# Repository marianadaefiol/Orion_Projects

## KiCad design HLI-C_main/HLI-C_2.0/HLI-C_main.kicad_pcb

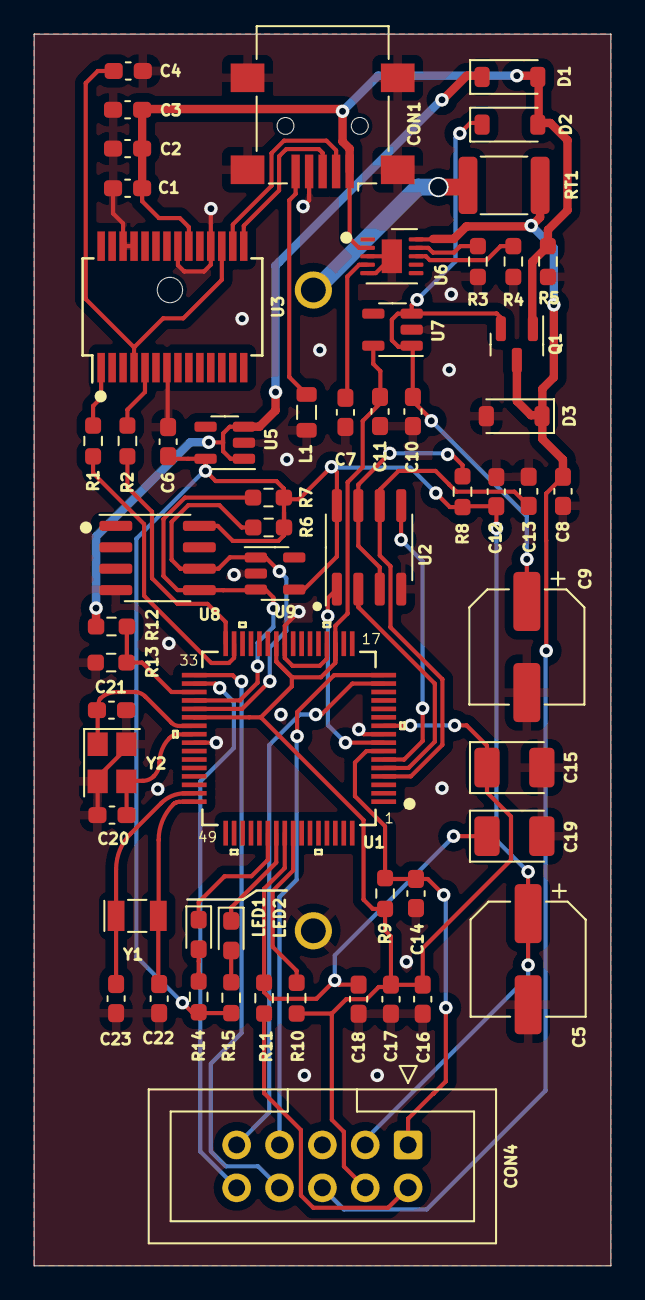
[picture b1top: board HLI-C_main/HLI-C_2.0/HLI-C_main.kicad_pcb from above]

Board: 2 copper layers, 34.2 x 73.0 mm, 59 parts (0 on the bottom side), 42 nets.

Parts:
C1, C6, C8, C10, C12, C16, C17, C18: 100nF; C_0603_1608Metric_Pad1.08x0.95mm_HandSolder
C2: 10nF; C_0603_1608Metric_Pad1.08x0.95mm_HandSolder
C3: 4,7uF; C_0603_1608Metric_Pad1.08x0.95mm_HandSolder
C4, C7, C11: 1uF; C_0603_1608Metric_Pad1.08x0.95mm_HandSolder
C5, C9: 220uFx16V; CP_Elec_6.3x7.7
C13: 47pF; C_0603_1608Metric_Pad1.08x0.95mm_HandSolder
C14: 1nF; C_0603_1608Metric_Pad1.08x0.95mm_HandSolder
C15: 10UfX6V-Tan; CP_EIA-3528-12_Kemet-T_Pad1.50x2.35mm_HandSolder
C19: 10uFx6V-Tan; CP_EIA-3528-12_Kemet-T_Pad1.50x2.35mm_HandSolder
C20, C21: 20pF; C_0603_1608Metric_Pad1.08x0.95mm_HandSolder
C22, C23: 12pF; C_0603_1608Metric_Pad1.08x0.95mm_HandSolder
CON1: USB_B; USB_Mini-B_Lumberg_2486_01_Horizontal
CON3: CR123A; BAT_BH123A
CON4: Conector_gravação; IDC-Header_2x05_P2.54mm_Vertical
D1, D2, D3: DSS14U; D_SOD-123
L1: BLM21PG221SN1D; L_0805_2012Metric
LED1: RED; LED_0603_1608Metric_Pad1.05x0.95mm_HandSolder
LED2: GREEN; LED_0603_1608Metric_Pad1.05x0.95mm_HandSolder
Q1: DMP3068L-7; SOT-23
R1, R2, R14, R15: 470R; R_0603_1608Metric_Pad0.98x0.95mm_HandSolder
R3: 10k; R_0603_1608Metric_Pad0.98x0.95mm_HandSolder
R4: 3.3k; R_0603_1608Metric_Pad0.98x0.95mm_HandSolder
R5, R8, R9: 22k; R_0603_1608Metric_Pad0.98x0.95mm_HandSolder
R6, R7, R11: 1K; R_0603_1608Metric_Pad0.98x0.95mm_HandSolder
R10: 22K; R_0603_1608Metric_Pad0.98x0.95mm_HandSolder
R12: 1K8; R_0603_1608Metric_Pad0.98x0.95mm_HandSolder
R13: 3K3; R_0603_1608Metric_Pad0.98x0.95mm_HandSolder
RT1: 300mA - 304N; R_1812_4532Metric
U1: PIC24HJ64GP206-I_PT; PIC24HJ64GP206-I_slash_PT
U2: FM25V10-GTR; SOIC-8_3.9x4.9mm_P1.27mm
U3: FT232RL; SSOP-28_5.3x10.2mm_P0.65mm
U5, U7: TPS7A0533PDBV; SOT-23-5
U6: LM3658SD; VSON-10-1EP_3x3mm_P0.5mm_EP1.2x2mm
U8: ATSHA204A-SSHDA-B; SOIC-8_3.9x4.9mm_P1.27mm
U9: 24AA02-OT; SOT-23-5
Y1: Crystal_32KHz; Crystal_SMD_MicroCrystal_CC7V-T1A-2Pin_3.2x1.5mm
Y2: Crystal_20MHz; Crystal_SMD_TXC_7M-4Pin_3.2x2.5mm

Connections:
0: C1.2, C2.2, C3.2, C4.2, C5.2, C6.2, C7.2, C8.2, C9.2, C10.2, C11.2, C12.2, C13.2, C14.2, C15.2, C16.2, C17.2, C18.2, C19.2, C20.2, C21.2, C22.2, C23.2, CON1.4 (GND), CON1.6, CON3.N, CON4.5, D3.2 (A), L1.1, R3.2, R4.1, R5.2, R13.1, U1.9 (VSS), U1.20 (AVSS), U1.25 (VSS), U1.41 (VSS), U2.4 (VSS), U3.7 (GND), U3.18 (GND), U3.21 (GND), U3.25 (AGND), U3.26 (TEST), U5.2 (GND), U6.3 (GND), U6.5 (EN_B), U6.11 (DAP), U7.2 (GND), U8.4 (GND), U9.2 (GND), Y2.2, Y2.4
+2V5: CON4.2, R11.1
+3.3VP: C11.1, C15.1, C16.1, C17.1, CON4.4, R9.1, R10.1, U1.10 (VDD), U1.19 (AVDD), U1.26 (VDD), U1.38 (VDD), U7.5 (OUT)
+3V3: C5.1, C6.1, C12.1, CON4.3, R6.1, R7.1, R8.1, R14.1, R15.1, U2.8 (VDD), U5.5 (OUT), U8.8 (VCC), U9.4 (VCC)
+5V: C1.1, C2.1, C3.1, CON1.1 (VBUS), D1.2 (A), D2.2 (A), Q1.1 (G), R5.1, U3.20 (VCC), U6.2 (USBPWR)
+5VD: D1.1 (K), R12.2, U5.1 (IN), U5.3 (EN)
LED2: LED1.1 (K), U1.54 (RD6)
LED3: LED2.1 (K), U1.55 (RD7)
unnamed: CON1.3 (D+), U3.15 (USBD+)
unnamed: CON1.2 (D-), U3.16 (USBD-)
unnamed: CON1.5 (Shield), L1.2
unnamed: C9.1, C10.1, D2.1 (K), Q1.2 (S), U7.1 (IN), U7.3 (EN)
unnamed: LED1.2 (A), R14.2
unnamed: LED2.2 (A), R15.2
unnamed: R10.2, U1.57 (VDD)
unnamed: U1.8 (*SS2/RG9), U2.1 (*S)
unnamed: C21.1, U1.39 (OSC1/CLKIN), Y2.1
unnamed: C20.1, U1.40 (OSC2/CLKO), Y2.3
unnamed: C23.1, U1.47 (RC13), Y1.1
unnamed: C22.1, U1.48 (RC14), Y1.2
unnamed: C13.1, U1.4 (SCK2/RG6), U2.6 (C)
unnamed: U1.5 (SDI2/RG7), U2.2 (Q)
unnamed: U1.6 (SDO2/RG8), U2.5 (D)
unnamed: C18.1, C19.1, R11.2, U1.56 (VDDCORE)
unnamed: R8.2, U2.3 (*W), U2.7 (*HOLD)
unnamed: C4.1, U3.4 (VCCIO), U3.17 (3V3OUT)
unnamed: R2.1, U3.5 (RXD)
unnamed: R1.1, U3.1 (TXD)
unnamed: R4.2, U6.8 (ISET)
unnamed: R3.1, U6.9 (TS)
unnamed: C7.1, U6.4 (USB_SEL)
PGEC2: CON4.9, U1.15 (RB1)
PGED2: CON4.7, U1.16 (RB0)
PIN-PWRMODE: R12.1, R13.2, U1.35 (RF6)
PIN-SCL: R6.2, U1.37 (SCL1/RG2), U8.6 (SCL), U9.1 (SCL)
PIN-SDA: R7.2, U1.36 (SDA1/RG3), U8.5 (SDA), U9.3 (SDA)
RESET: C14.1, CON4.1, R9.2, U1.7 (*MCLR)
RXA: R2.2, U1.32 (U2TX/RF5)
RXB: CON4.8, U1.33 (U1TX/RF3)
TXA: R1.2, U1.31 (U2RX/RF4)
TXB: CON4.10, U1.34 (U1RX/RF2)
VBAT: C8.1, CON4.6, D3.1 (K), Q1.3 (D), RT1.2, U6.10 (BATT)

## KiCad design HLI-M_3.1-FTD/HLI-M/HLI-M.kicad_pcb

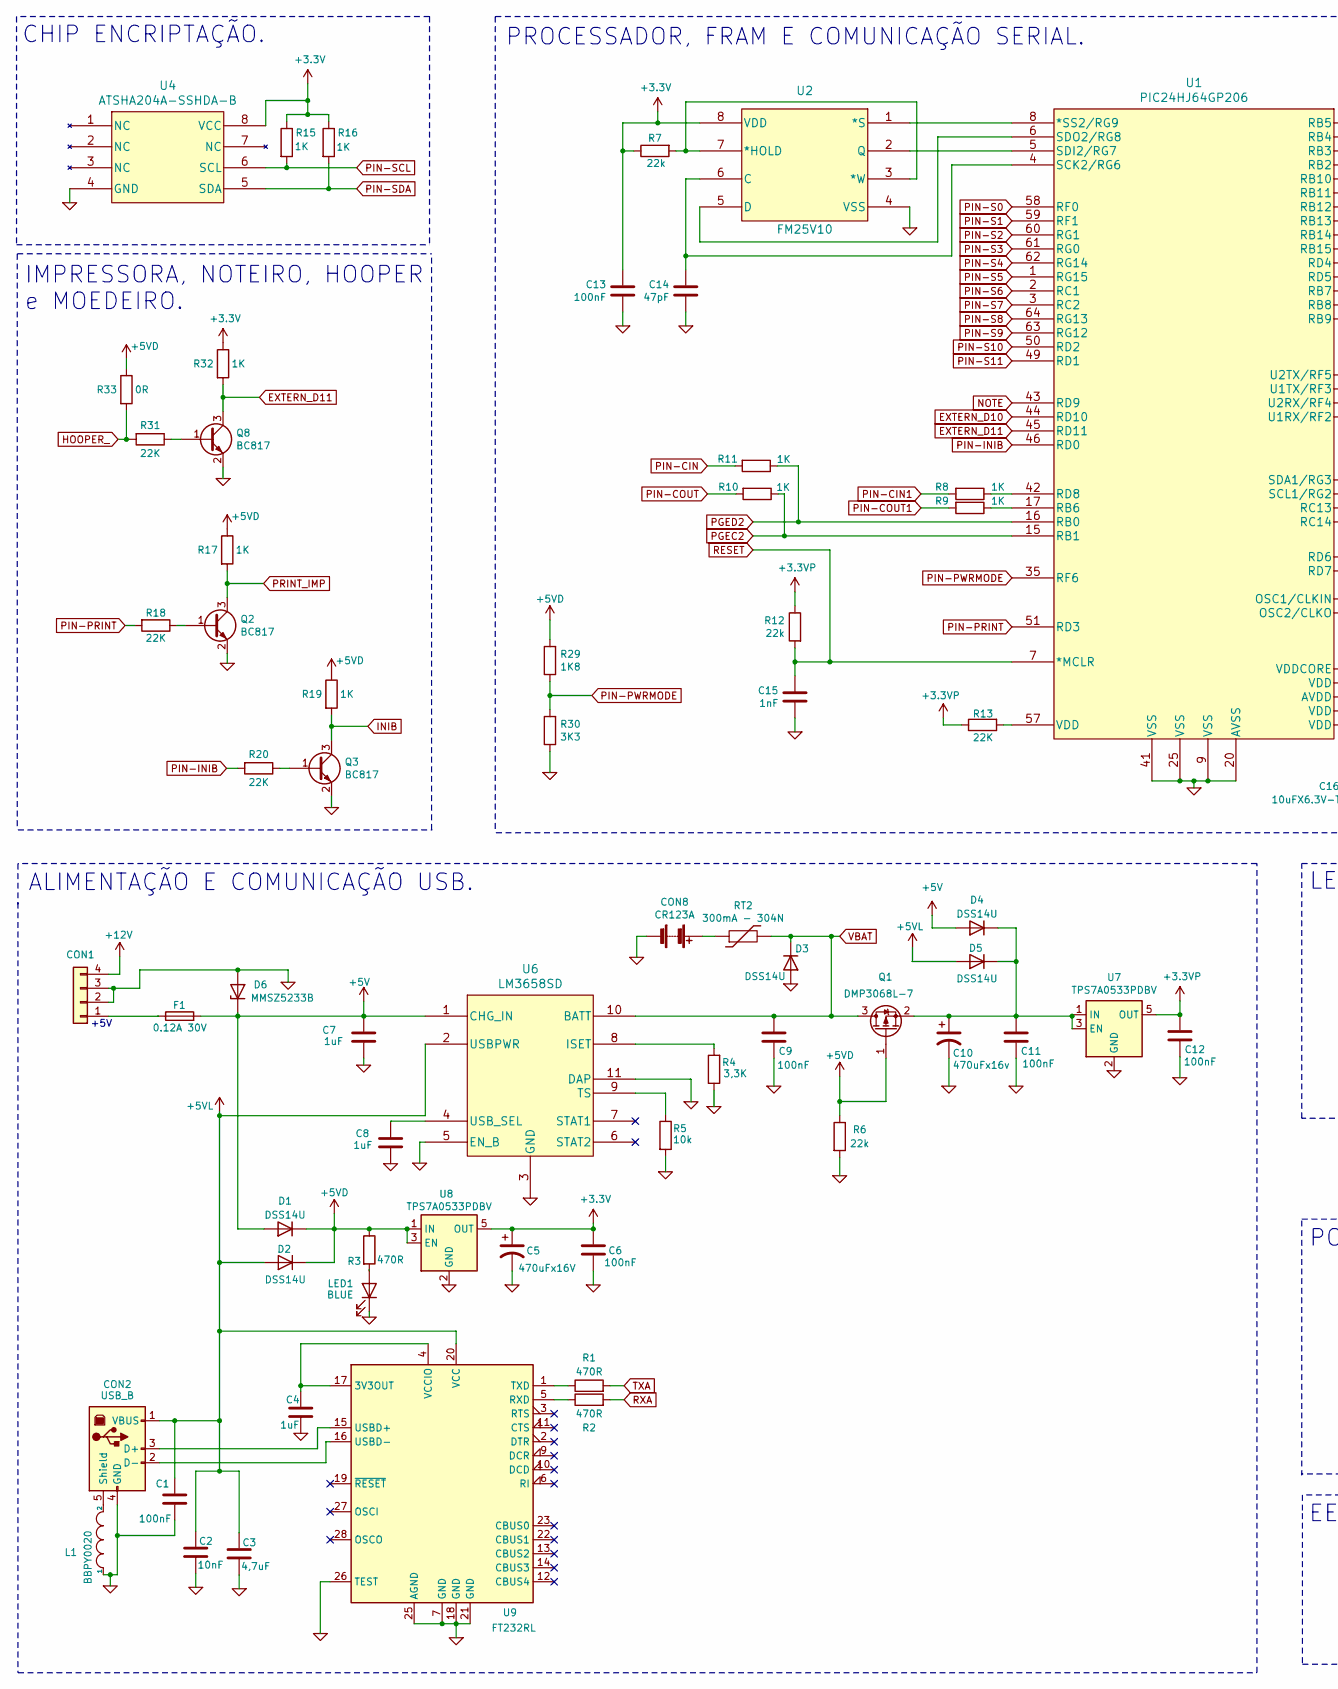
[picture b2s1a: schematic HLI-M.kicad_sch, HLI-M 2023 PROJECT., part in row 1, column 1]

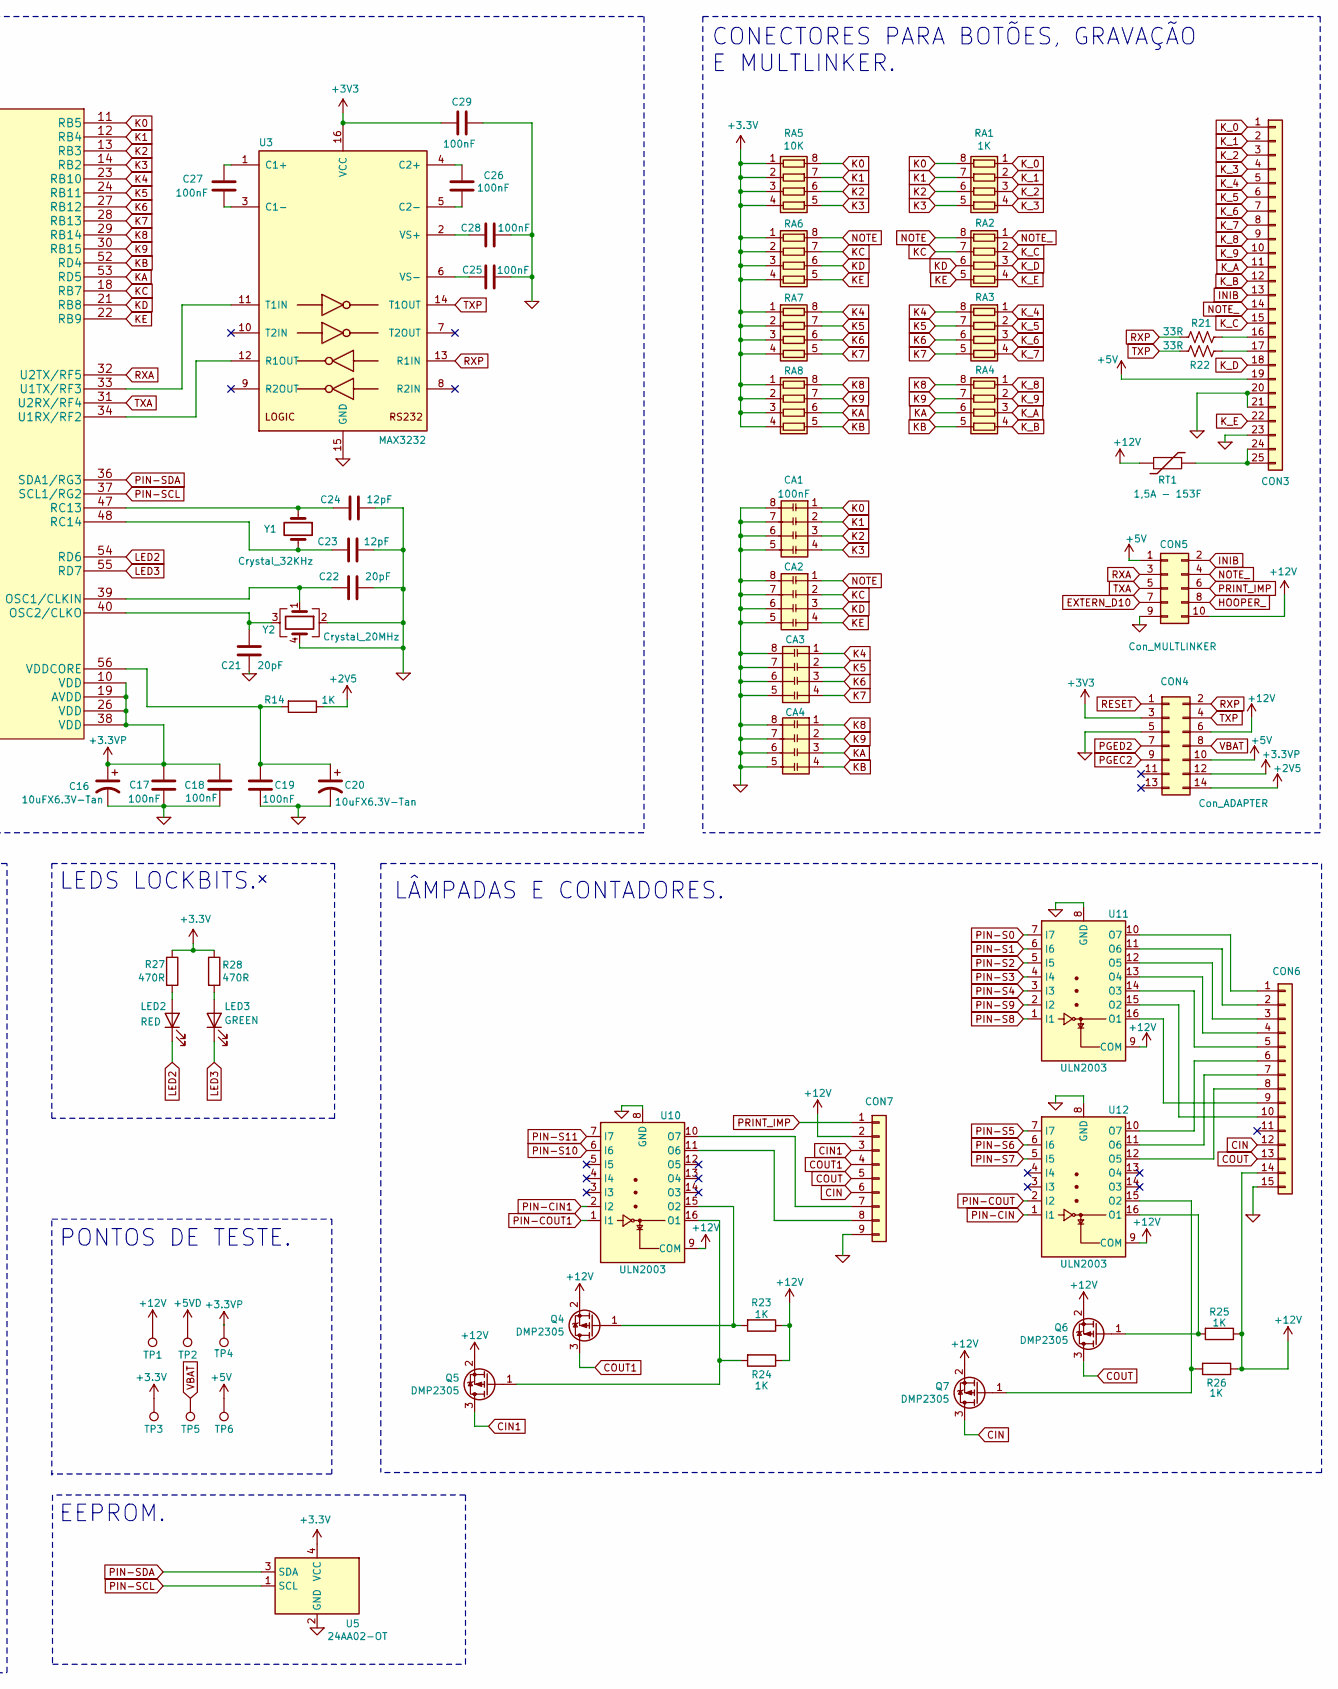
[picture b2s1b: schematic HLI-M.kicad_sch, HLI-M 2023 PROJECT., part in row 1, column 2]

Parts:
C1, C6, C9, C11, C12, C13, C17, C18, C19, C25, C26, C27, C28, C29: 100nF; C_0603_1608Metric_Pad1.08x0.95mm_HandSolder
C2: 10nF; C_0603_1608Metric_Pad1.08x0.95mm_HandSolder
C3: 4,7uF; C_0603_1608Metric_Pad1.08x0.95mm_HandSolder
C4, C7, C8: 1uF; C_0603_1608Metric_Pad1.08x0.95mm_HandSolder
C5: 470uFx16V; CP_Elec_10x10.5
C10: 470uFx16v; CP_Elec_10x10.5
C14: 47pF; C_0603_1608Metric_Pad1.08x0.95mm_HandSolder
C15: 1nF; C_0603_1608Metric_Pad1.08x0.95mm_HandSolder
C16, C20: 10uFX6.3V-Tan; CP_EIA-3528-12_Kemet-T_Pad1.50x2.35mm_HandSolder
C21, C22: 20pF; C_0603_1608Metric_Pad1.08x0.95mm_HandSolder
C23, C24: 12pF; C_0603_1608Metric_Pad1.08x0.95mm_HandSolder
CA1: 100nF; R_Array_Convex_4x0603
CA2, CA3, CA4: Array_Cap; R_Array_Convex_4x0603
CON1: Molex-0015244449-0
CON2: USB_B; USB_B_Lumberg_2411_02_Horizontal
CON3: DSUB-25_Male_Vertical_P2.77x2.84mm_MountingHoles
CON4: Con_ADAPTER; IDC-Header_2x07_P2.54mm_Horizontal
CON5: Con_MULTLINKER; IDC-Header_2x05_P2.54mm_Horizontal
CON6: Conn_01x15; DSUB-15_Female_Vertical_P2.77x2.84mm_MountingHoles
CON7: Conn_01x09; DSUB-9_Female_Vertical_P2.77x2.84mm_MountingHoles
CON8: CR123A; BAT_BH123A
D1, D2, D4, D5: DSS14U; D_SOD-123
D3: DSS14U; D_2010_5025Metric
D6: MMSZ5233B
F1: 0.12A 30V; Fuse_1812_4532Metric
L1: BBPY0020; L_0805_2012Metric
LED1: BLUE; LED_0603_1608Metric_Pad1.05x0.95mm_HandSolder
LED2: RED; LED_0603_1608Metric_Pad1.05x0.95mm_HandSolder
LED3: GREEN; LED_0603_1608Metric_Pad1.05x0.95mm_HandSolder
Q1: DMP3068L-7; SOT-23
Q2, Q3, Q8: BC817; SOT-23
Q4, Q5, Q6, Q7: DMP2305; SOT-23
R1, R2, R3, R27, R28: 470R; R_0603_1608Metric_Pad0.98x0.95mm_HandSolder
R4: 3,3K; R_0603_1608Metric_Pad0.98x0.95mm_HandSolder
R5: 10k; R_0603_1608Metric_Pad0.98x0.95mm_HandSolder
R6, R7, R12: 22k; R_0603_1608Metric_Pad0.98x0.95mm_HandSolder
R8, R9, R10, R11, R14, R15, R16, R17, R19, R23, R24, R25, R26, R32: 1K; R_0603_1608Metric_Pad0.98x0.95mm_HandSolder
R13, R18, R20, R31: 22K; R_0603_1608Metric_Pad0.98x0.95mm_HandSolder
R21, R22: 33R; R_0603_1608Metric_Pad0.98x0.95mm_HandSolder
R29: 1K8; R_0603_1608Metric_Pad0.98x0.95mm_HandSolder
R30: 3K3; R_0603_1608Metric_Pad0.98x0.95mm_HandSolder
R33: 0R; R_0603_1608Metric_Pad0.98x0.95mm_HandSolder
RA1: 1K; R_Array_Convex_4x0603
RA2, RA3, RA4, RA6, RA7, RA8: R_Pack04; R_Array_Convex_4x0603
RA5: 10K; R_Array_Convex_4x0603
RT1: 1,5A - 153F; R_1812_4532Metric
RT2: 300mA - 304N; R_1812_4532Metric
TP1: TestPoint; TestPoint_Pad_1.5x1.5mm
TP2, TP6: TestPoint; TestPoint_Pad_D1.5mm
TP3, TP4, TP5: TestPoint; TestPoint_Pad_D1.0mm
U1: PIC24HJ64GP206; TQFP-64_10x10mm_P0.5mm
U2: FM25V10; FM25V10-GTR
U3: MAX3232; SOIC-16_3.9x9.9mm_P1.27mm
U4: ATSHA204A-SSHDA-B; SOIC-8_3.9x4.9mm_P1.27mm
U5: 24AA02-OT; SOT-23-5
U6: LM3658SD
U7, U8: TPS7A0533PDBV; SOT-23-5
U9: FT232RL; SSOP-28_5.3x10.2mm_P0.65mm
U10, U11, U12: ULN2003; SOIC-16_3.9x9.9mm_P1.27mm
Y1: Crystal_32KHz; Crystal_SMD_MicroCrystal_CC7V-T1A-2Pin_3.2x1.5mm
Y2: Crystal_20MHz; Crystal_SMD_TXC_7M-4Pin_3.2x2.5mm

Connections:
0: C1.2, C2.2, C3.2, C4.2, C5.2, C6.2, C7.2, C8.2, C9.2, C10.2, C11.2, C12.2, C13.2, C14.2, C15.2, C16.2, C17.2, C18.2, C19.2, C20.2, C21.2, C22.2, C23.2, C24.2, C25.2, C28.2, C29.2, CA1.5, CA1.6, CA1.7, CA1.8, CA2.5, CA2.6, CA2.7, CA2.8, CA3.5, CA3.6, CA3.7, CA3.8, CA4.5, CA4.6, CA4.7, CA4.8, CON1.2, CON1.3, CON2.4 (GND), CON3.20, CON3.21, CON3.23, CON4.5, CON5.9, CON6.15, CON7.9, CON8.2 (-), CON8.N, D3.2 (A), D6.2 (A), L1.1, LED1.1 (K), Q2.2 (E), Q3.2 (E), Q8.2 (E), R4.1, R5.2, R6.2, R30.1, U1.9 (VSS), U1.20 (AVSS), U1.25 (VSS), U1.41 (VSS), U2.4 (VSS), U3.15 (GND), U4.4 (GND), U5.2 (GND), U6.3 (GND), U6.5 (EN_B), U6.11 (DAP), U7.2 (GND), U8.2 (GND), U9.7 (GND), U9.18 (GND), U9.21 (GND), U9.25 (AGND), U9.26 (TEST), U10.8 (GND), U11.8 (GND), U12.8 (GND), Y2.2, Y2.4; also elsewhere on the board
+2V5: CON4.14, R14.1
+3.3VP: C12.1, C16.1, C17.1, C18.1, CON4.12, R12.1, R13.1, TP4.1, U1.10 (VDD), U1.19 (AVDD), U1.26 (VDD), U1.38 (VDD), U7.5 (OUT)
+5V: C7.1, CON3.19, CON4.10, CON5.1, D1.2 (A), D4.2 (A), D6.1 (K), F1.2, TP6.1, U6.1 (CHG_IN)
+5VD: D1.1 (K), D2.1 (K), Q1.1 (G), R3.1, R6.1, R17.1, R19.1, R29.2, R33.1, TP2.1, U8.1 (IN), U8.3 (EN)
+5VL: C1.1, C2.1, C3.1, CON2.1 (VBUS), D2.2 (A), D5.2 (A), U6.2 (USBPWR), U9.20 (VCC)
+12V: CON1.4, CON4.6, CON5.10, CON6.14, CON7.2, Q4.2 (S), Q5.2 (S), Q6.2 (S), Q7.2 (S), R23.1, R24.1, R25.1, R26.1, RT1.2, TP1.1, U10.9 (COM), U11.9 (COM), U12.9 (COM)
CIN: CON6.12, CON7.6, Q7.3 (D)
CIN1: CON7.3, Q5.3 (D)
COUT: CON6.13, CON7.5, Q6.3 (D)
COUT1: CON7.4, Q4.3 (D)
EXTERN_D10: CON5.7, U1.44 (RD10)
EXTERN_D11: Q8.3 (C), R32.2, U1.45 (RD11)
HOOPER_: CON5.8, R31.2, R33.2
INIB: CON3.13, CON5.2, Q3.3 (C), R19.2
K0: CA1.1, RA1.8 (R1.2), RA5.8 (R1.2), U1.11 (RB5)
K1: CA1.2, RA1.7 (R2.2), RA5.7 (R2.2), U1.12 (RB4)
K2: CA1.3, RA1.6 (R3.2), RA5.6 (R3.2), U1.13 (RB3)
K3: CA1.4, RA1.5 (R4.2), RA5.5 (R4.2), U1.14 (RB2)
K4: CA3.1, RA3.8 (R1.2), RA7.8 (R1.2), U1.23 (RB10)
K5: CA3.2, RA3.7 (R2.2), RA7.7 (R2.2), U1.24 (RB11)
K6: CA3.3, RA3.6 (R3.2), RA7.6 (R3.2), U1.27 (RB12)
K7: CA3.4, RA3.5 (R4.2), RA7.5 (R4.2), U1.28 (RB13)
K8: CA4.1, RA4.8 (R1.2), RA8.8 (R1.2), U1.29 (RB14)
K9: CA4.2, RA4.7 (R2.2), RA8.7 (R2.2), U1.30 (RB15)
KA: CA4.3, RA4.6 (R3.2), RA8.6 (R3.2), U1.53 (RD5)
KB: CA4.4, RA4.5 (R4.2), RA8.5 (R4.2), U1.52 (RD4)
KC: CA2.2, RA2.7 (R2.2), RA6.7 (R2.2), U1.18 (RB7)
KD: CA2.3, RA2.6 (R3.2), RA6.6 (R3.2), U1.21 (RB8)
KE: CA2.4, RA2.5 (R4.2), RA6.5 (R4.2), U1.22 (RB9)
K_0: CON3.1, RA1.1 (R1.1)
K_1: CON3.2, RA1.2 (R2.1)
K_2: CON3.3, RA1.3 (R3.1)
K_3: CON3.4, RA1.4 (R4.1)
K_4: CON3.5, RA3.1 (R1.1)
K_5: CON3.6, RA3.2 (R2.1)
K_6: CON3.7, RA3.3 (R3.1)
K_7: CON3.8, RA3.4 (R4.1)
K_8: CON3.9, RA4.1 (R1.1)
K_9: CON3.10, RA4.2 (R2.1)
K_A: CON3.11, RA4.3 (R3.1)
K_B: CON3.12, RA4.4 (R4.1)
K_C: CON3.15, RA2.2 (R2.1)
K_D: CON3.18, RA2.3 (R3.1)
K_E: CON3.22, RA2.4 (R4.1)
LED2: LED2.1 (K), U1.54 (RD6)
LED3: LED3.1 (K), U1.55 (RD7)
NOTE: CA2.1, RA2.8 (R1.2), RA6.8 (R1.2), U1.43 (RD9)
NOTE_: CON3.14, CON5.4, RA2.1 (R1.1)
unnamed: CON1.1, F1.1
unnamed: CON2.3 (D+), U9.15 (USBD+)
unnamed: CON2.2 (D-), U9.16 (USBD-)
unnamed: CON2.5 (Shield), L1.2
unnamed: CON3.16, R21.2
unnamed: CON3.17, R22.2
unnamed: CON3.24, CON3.25, RT1.1
unnamed: CON6.1, U11.10 (O7)
unnamed: CON6.2, U11.11 (O6)
unnamed: CON6.3, U11.12 (O5)
unnamed: CON6.4, U11.13 (O4)
unnamed: CON6.5, U11.14 (O3)
unnamed: CON6.6, U12.10 (O7)
unnamed: CON6.7, U12.11 (O6)
unnamed: CON6.8, U12.12 (O5)
unnamed: CON6.9, U11.16 (O1)
unnamed: CON6.10, U11.15 (O2)
unnamed: CON7.7, U10.10 (O7)
unnamed: CON7.8, U10.11 (O6)
unnamed: CON8.1 (+), RT2.1
unnamed: C10.1, C11.1, D4.1 (K), D5.1 (K), Q1.2 (S), U7.1 (IN), U7.3 (EN)
unnamed: LED1.2 (A), R3.2
unnamed: LED2.2 (A), R27.2
unnamed: LED3.2 (A), R28.2
unnamed: Q2.1 (B), R18.1
unnamed: Q3.1 (B), R20.1
unnamed: Q4.1 (G), R23.2, U10.15 (O2)
unnamed: Q5.1 (G), R24.2, U10.16 (O1)
unnamed: Q6.1 (G), R25.2, U12.16 (O1)
unnamed: Q7.1 (G), R26.2, U12.15 (O2)
unnamed: Q8.1 (B), R31.1
unnamed: R13.2, U1.57 (VDD)
unnamed 81: U1.8 (*SS2/RG9), U2.1 (*S); also elsewhere on the board
unnamed: C22.1, U1.39 (OSC1/CLKIN), Y2.1
unnamed: C21.1, U1.40 (OSC2/CLKO), Y2.3
unnamed: R9.1, U1.17 (RB6)
unnamed: C24.1, U1.47 (RC13), Y1.1
unnamed: C23.1, U1.48 (RC14), Y1.2
unnamed: R8.1, U1.42 (RD8)
unnamed 88: C14.1, U1.4 (SCK2/RG6), U2.6 (C); also elsewhere on the board
unnamed 89: U1.5 (SDI2/RG7), U2.2 (Q); also elsewhere on the board
unnamed 90: U1.6 (SDO2/RG8), U2.5 (D); also elsewhere on the board
unnamed: U1.34 (U1RX/RF2), U3.12 (R1OUT)
unnamed: U1.33 (U1TX/RF3), U3.11 (T1IN)
unnamed: C19.1, C20.1, R14.2, U1.56 (VDDCORE)
unnamed 94: R7.2, U2.3 (*W), U2.7 (*HOLD); also elsewhere on the board
unnamed: C27.1, U3.1 (C1+)
unnamed: C27.2, U3.3 (C1-)
unnamed: C26.1, U3.4 (C2+)
unnamed: C26.2, U3.5 (C2-)
unnamed: C28.1, U3.2 (VS+)
unnamed: C25.1, U3.6 (VS-)
unnamed: R4.2, U6.8 (ISET)
unnamed: R5.1, U6.9 (TS)
unnamed: C8.1, U6.4 (USB_SEL)
unnamed: C4.1, U9.4 (VCCIO), U9.17 (3V3OUT)
unnamed: R2.1, U9.5 (RXD)
unnamed: R1.1, U9.1 (TXD)
PGEC2: CON4.9, R10.1, U1.15 (RB1)
PGED2: CON4.7, R11.1, U1.16 (RB0)
PIN-CIN: R11.2, U12.1 (I1)
PIN-CIN1: R8.2, U10.2 (I2)
PIN-COUT: R10.2, U12.2 (I2)
PIN-COUT1: R9.2, U10.1 (I1)
PIN-INIB: R20.2, U1.46 (RD0)
PIN-PRINT: R18.2, U1.51 (RD3)
PIN-PWRMODE: R29.1, R30.2, U1.35 (RF6)
PIN-S0: U1.58 (RF0), U11.7 (I7)
PIN-S1: U1.59 (RF1), U11.6 (I6)
PIN-S2: U1.60 (RG1), U11.5 (I5)
PIN-S3: U1.61 (RG0), U11.4 (I4)
PIN-S4: U1.62 (RG14), U11.3 (I3)
PIN-S5: U1.1 (RG15), U12.7 (I7)
PIN-S6: U1.2 (RC1), U12.6 (I6)
PIN-S7: U1.3 (RC2), U12.5 (I5)
PIN-S8: U1.64 (RG13), U11.1 (I1)
PIN-S9: U1.63 (RG12), U11.2 (I2)
PIN-S10: U1.50 (RD2), U10.6 (I6)
PIN-S11: U1.49 (RD1), U10.7 (I7)
PIN-SCL: R15.2, U1.37 (SCL1/RG2), U4.6 (SCL), U5.1 (SCL); also elsewhere on the board
PIN-SDA: R16.2, U1.36 (SDA1/RG3), U4.5 (SDA), U5.3 (SDA); also elsewhere on the board
PRINT_IMP: CON5.6, CON7.1, Q2.3 (C), R17.2
RESET: C15.1, CON4.1, R12.2, U1.7 (*MCLR)
RXA: CON5.3, R2.2, U1.32 (U2TX/RF5)
RXP: CON4.2, R21.1, U3.13 (R1IN)
TXA: CON5.5, R1.2, U1.31 (U2RX/RF4)
TXP: CON4.4, R22.1, U3.14 (T1OUT)
VBAT: C9.1, CON4.8, D3.1 (K), Q1.3 (D), RT2.2, TP5.1, U6.10 (BATT)

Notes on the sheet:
PROCESSADOR, FRAM E COMUNICAÇÃO SERIAL.
+5V
EEPROM.
CONECTORES PARA BOTÕES, GRAVAÇÃO E MULTLINKER.
IMPRESSORA, NOTEIRO, HOOPER e MOEDEIRO.
ALIMENTAÇÃO E COMUNICAÇÃO USB.
PONTOS DE TESTE.
LÂMPADAS E CONTADORES.
LEDS LOCKBITS.
CHIP ENCRIPTAÇÃO.

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
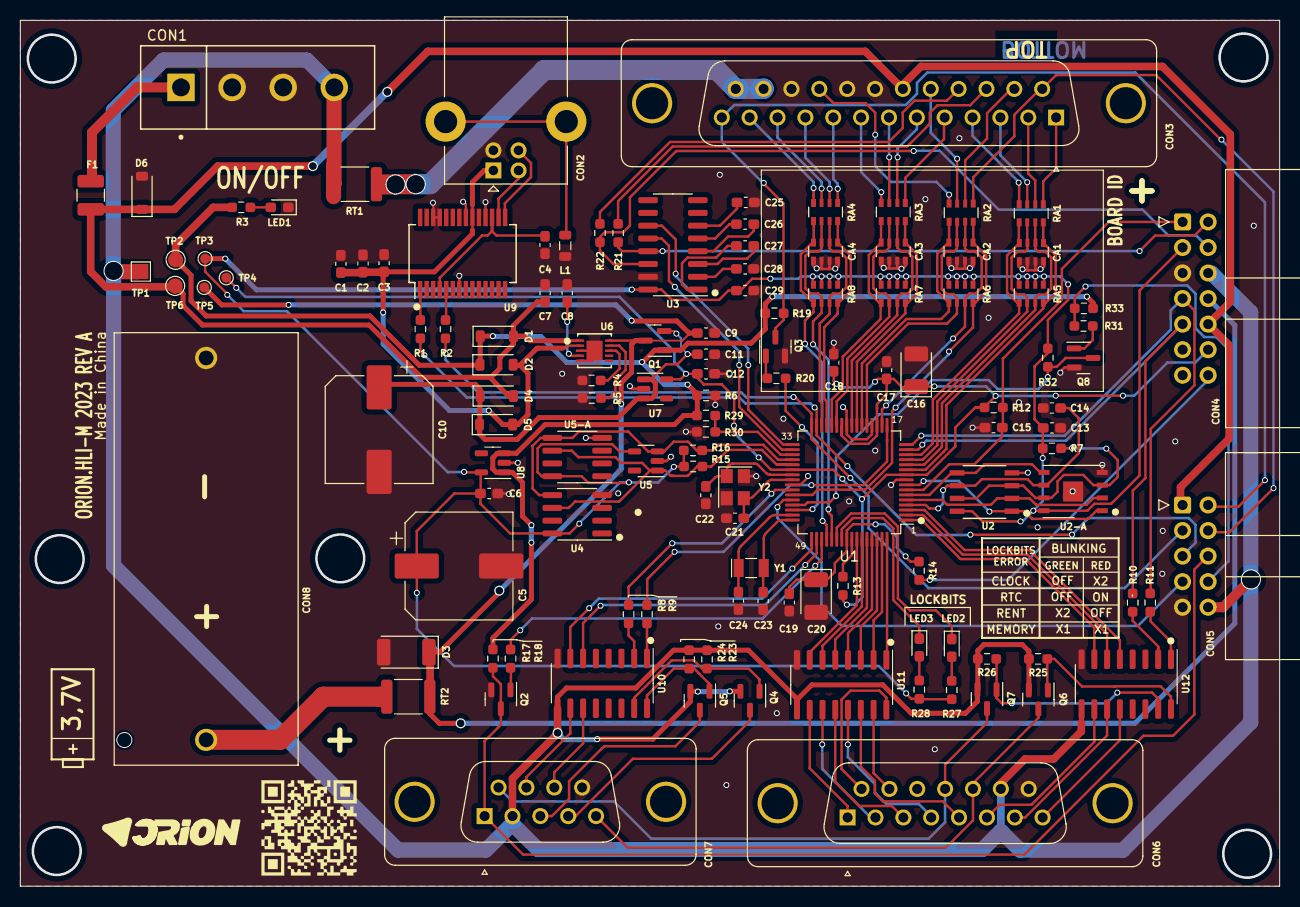
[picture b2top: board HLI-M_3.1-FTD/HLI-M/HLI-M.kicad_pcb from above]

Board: 2 copper layers, 125.2 x 86.1 mm, 125 parts (0 on the bottom side), 137 nets.

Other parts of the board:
U2-A: DFN-8-1EP_6x5mm_P1.27mm_EP2x2mm
U5-A: SOIC-8_3.9x4.9mm_P1.27mm

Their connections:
0: U2-A.4, U2-A.9, U5-A.4; also elsewhere on the board
unnamed 81: U2-A.1; also elsewhere on the board
unnamed 88: U2-A.6; also elsewhere on the board
unnamed 89: U2-A.2; also elsewhere on the board
unnamed 90: U2-A.5; also elsewhere on the board
unnamed 94: U2-A.3, U2-A.7; also elsewhere on the board
PIN-SCL: U5-A.6; also elsewhere on the board
PIN-SDA: U5-A.5; also elsewhere on the board

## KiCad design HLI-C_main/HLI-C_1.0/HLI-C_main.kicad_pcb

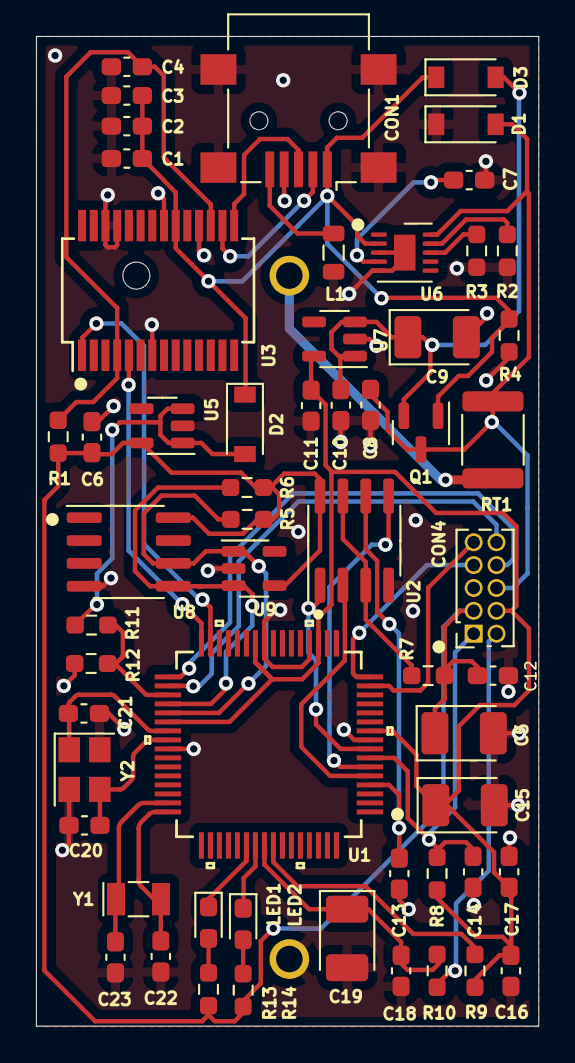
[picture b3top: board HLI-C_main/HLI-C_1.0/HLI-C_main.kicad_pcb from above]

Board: 2 copper layers, 27.9 x 55.0 mm, 59 parts (0 on the bottom side), 40 nets.

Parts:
C1, C6, C8, C10, C11, C12, C16, C17, C18: 100nF; C_0603_1608Metric_Pad1.08x0.95mm_HandSolder
C2: 10nF; C_0603_1608Metric_Pad1.08x0.95mm_HandSolder
C3: 4,7uF; C_0603_1608Metric_Pad1.08x0.95mm_HandSolder
C4, C7: 1uF; C_0603_1608Metric_Pad1.08x0.95mm_HandSolder
C5: 220uFx16V; CP_EIA-3528-12_Kemet-T_Pad1.50x2.35mm_HandSolder
C9: 470uFx16v; CP_EIA-3528-12_Kemet-T_Pad1.50x2.35mm_HandSolder
C13: 47pF; C_0603_1608Metric_Pad1.08x0.95mm_HandSolder
C14: 1nF; C_0603_1608Metric_Pad1.08x0.95mm_HandSolder
C15: 10UfX6V-Tan; CP_EIA-3528-12_Kemet-T_Pad1.50x2.35mm_HandSolder
C19: 10uFx6V-Tan; CP_EIA-3528-12_Kemet-T_Pad1.50x2.35mm_HandSolder
C20, C21: 10pF; C_0603_1608Metric_Pad1.08x0.95mm_HandSolder
C22, C23: 7pF; C_0603_1608Metric_Pad1.08x0.95mm_HandSolder
CON1: USB_B; USB_Mini-B_Lumberg_2486_01_Horizontal
CON3: CR123A; BAT_BH123A
CON4: Conn_02x05_Odd_Even; PinSocket_2x05_P1.27mm_Vertical
D1, D2, D3: SSA33L; D_SOD-123
G1: LOGO
L1: BLM21PG221SN1D; L_0805_2012Metric
LED1: RED; LED_0603_1608Metric_Pad1.05x0.95mm_HandSolder
LED2: GREEN; LED_0603_1608Metric_Pad1.05x0.95mm_HandSolder
Q1: IRLML5103; SOT-23
R1: 0R; R_0603_1608Metric_Pad0.98x0.95mm_HandSolder
R2, R3, R4: 10k; R_0603_1608Metric_Pad0.98x0.95mm_HandSolder
R5, R6, R10: 1K; R_0603_1608Metric_Pad0.98x0.95mm_HandSolder
R7, R8: 22k; R_0603_1608Metric_Pad0.98x0.95mm_HandSolder
R9: 22K; R_0603_1608Metric_Pad0.98x0.95mm_HandSolder
R11: 1K5; R_0603_1608Metric_Pad0.98x0.95mm_HandSolder
R12: 3K3; R_0603_1608Metric_Pad0.98x0.95mm_HandSolder
R13, R14: 470R; R_0603_1608Metric_Pad0.98x0.95mm_HandSolder
RT1: 300mA - 304N; R_1812_4532Metric
U1: PIC24HJ64GP206-I_PT; PIC24HJ64GP206-I_slash_PT
U2: FM25V10-GTR; SOIC-8_3.9x4.9mm_P1.27mm
U3: FT232RL; SSOP-28_5.3x10.2mm_P0.65mm
U5, U7: TPS7A0533PDBV; SOT-23-5
U6: LM3658SD; VSON-10-1EP_3x3mm_P0.5mm_EP1.2x2mm
U8: ATSHA204A-SSHDA-B; SOIC-8_3.9x4.9mm_P1.27mm
U9: 24AA02-OT; SOT-23-5
Y1: Crystal_32KHz; Crystal_SMD_MicroCrystal_CC7V-T1A-2Pin_3.2x1.5mm
Y2: Crystal_20MHz; Crystal_SMD_TXC_7M-4Pin_3.2x2.5mm

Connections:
0: C1.2, C2.2, C3.2, C4.2, C5.2, C6.2, C7.2, C8.2, C9.2, C10.2, C11.2, C12.2, C13.2, C14.2, C15.2, C16.2, C17.2, C18.2, C19.2, C20.2, C21.2, C22.2, C23.2, CON1.4 (GND), CON1.6, CON3.N, D1.1 (K), L1.1, R2.2, R3.1, R4.2, R12.1, U1.9 (VSS), U1.20 (AVSS), U1.25 (VSS), U1.41 (VSS), U2.4 (VSS), U3.7 (GND), U3.18 (GND), U3.21 (GND), U3.25 (AGND), U3.26 (TEST), U5.2 (GND), U6.3 (GND), U6.5 (EN_B), U7.2 (GND), U8.4 (GND), U9.2 (GND), Y2.2, Y2.4
+2V5: CON4.2, R10.1
+3.3VP: C11.1, C15.1, C16.1, C17.1, CON4.4, R8.1, R9.1, U1.10 (VDD), U1.19 (AVDD), U1.26 (VDD), U1.38 (VDD), U7.5 (OUT)
+3V3: C5.1, C6.1, C12.1, CON4.3, R1.1, R5.1, R6.1, R7.1, R13.1, R14.1, U2.8 (VDD), U5.5 (OUT), U8.8 (VCC), U9.4 (VCC)
+5V: C1.1, C2.1, C3.1, CON1.1 (VBUS), D2.1 (K), D3.1 (K), Q1.1 (G), R4.1, U3.20 (VCC), U6.2 (USBPWR)
+5VD: D2.2 (A), R11.2, U5.1 (IN), U5.3 (EN)
LED2: LED1.1 (K), U1.54 (RD6)
LED3: LED2.1 (K), U1.55 (RD7)
unnamed: C4.1, R1.2, U3.4 (VCCIO), U3.17 (3V3OUT)
unnamed: C7.1, U6.4 (USB_SEL)
unnamed: C9.1, C10.1, D3.2 (A), Q1.2 (S), U7.1 (IN), U7.3 (EN)
unnamed: C13.1, U1.4 (SCK2/RG6), U2.6 (C)
unnamed: C18.1, C19.1, R10.2, U1.56 (VDDCORE)
unnamed: C20.1, U1.40 (OSC2/CLKO), Y2.3
unnamed: C21.1, U1.39 (OSC1/CLKIN), Y2.1
unnamed: C22.1, U1.48 (RC14), Y1.1
unnamed: C23.1, U1.47 (RC13), Y1.2
unnamed: CON1.2 (D-), U3.16 (USBD-)
unnamed: CON1.3 (D+), U3.15 (USBD+)
unnamed: CON1.5 (Shield), L1.2
unnamed: LED1.2 (A), R13.2
unnamed: LED2.2 (A), R14.2
unnamed: R2.1, U6.9 (TS)
unnamed: R3.2, U6.8 (ISET)
unnamed: R7.2, U2.3 (*W), U2.7 (*HOLD)
unnamed: R9.2, U1.57 (VDD)
unnamed: U1.5 (SDI2/RG7), U2.2 (Q)
unnamed: U1.6 (SDO2/RG8), U2.5 (D)
unnamed: U1.8 (*SS2/RG9), U2.1 (*S)
PGEC2: CON4.9, U1.15 (RB1)
PGED2: CON4.7, U1.16 (RB0)
PIN-PWRMODE: R11.1, R12.2, U1.35 (RF6)
PIN-SCL: R5.2, U1.37 (SCL1/RG2), U8.6 (SCL), U9.1 (SCL)
PIN-SDA: R6.2, U1.36 (SDA1/RG3), U8.5 (SDA), U9.3 (SDA)
RESET: C14.1, CON4.1, R8.2, U1.7 (*MCLR)
RXA: U1.32 (U2TX/RF5), U3.5 (RXD)
RXB: CON4.8, U1.33 (U1TX/RF3)
TXA: U1.31 (U2RX/RF4), U3.1 (TXD)
TXB: CON4.10, U1.34 (U1RX/RF2)
VBAT: C8.1, CON4.6, D1.2 (A), Q1.3 (D), RT1.2, U6.10 (BATT)

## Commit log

2022-09-19 att hli-m FTD
2022-11-03 att2
2023-02-14 new orion
2023-03-06 att circuito HLI-C
2023-03-07 atualizado com versoes de board
2023-03-07 versões HLI-C atualizadas
2023-03-07 inicio alteracoes HLI-C
2023-03-09 circuito HLI-C finalizado, precisa de revisao
2023-03-10 atualizado hli-m, precisa de revisao
2023-03-15 atualizado com bot pra ligar HLI
2023-03-20 Create Amp_audio
2023-04-05 att projeto
2023-04-17 atualização circuito FTD e 3D
2023-04-18 HLI-M_2023: circuito atualizado e revisado.
2023-04-18 HLI-C 2023: atualizado e revisado.
2023-04-19 atualização serigrafia e conector bateria
2023-04-20 novos arquivos para estudar
2023-06-06 atualizado 6/6 HLI-M
2023-07-04 arquivo BOOM hli-m
2023-07-04 arquivo xsl
2023-07-04 BOOM HLI-M 2023
    enviado para fabricante.
2023-08-04 reconfigurando a zona de configuração do chip
2023-08-07 att geraçao de SHA-256
2023-08-14 atualizado
2023-08-18 adicionando arquivo SHA-256
2023-08-21 refacture config zone
2023-08-28 configuration 2.0
2023-10-05 versao atualizada

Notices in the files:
parts and their libraries:
Copyright 2016 Accelerated Designs. All rights reserved.
